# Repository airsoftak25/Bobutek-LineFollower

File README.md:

# Team
- Vadim Sobčuk - Modeling / Elektro
- Daniel Pelikán - Code / Elektro
- Luboš Stránský - PCB Manufacture
# Description
We are czech students from High school - prumyslova skola prosek - that enjoy making robots in the free time,

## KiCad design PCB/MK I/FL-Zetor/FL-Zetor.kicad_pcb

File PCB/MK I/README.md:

# About
This Folder Holds DWG file (edge cuts), exel files with components, gerber files (Main and Senzor) and Kicad Projects of LF-Zetro MKI 

Maded by Bobutek team with help from Otto von Bismax :D

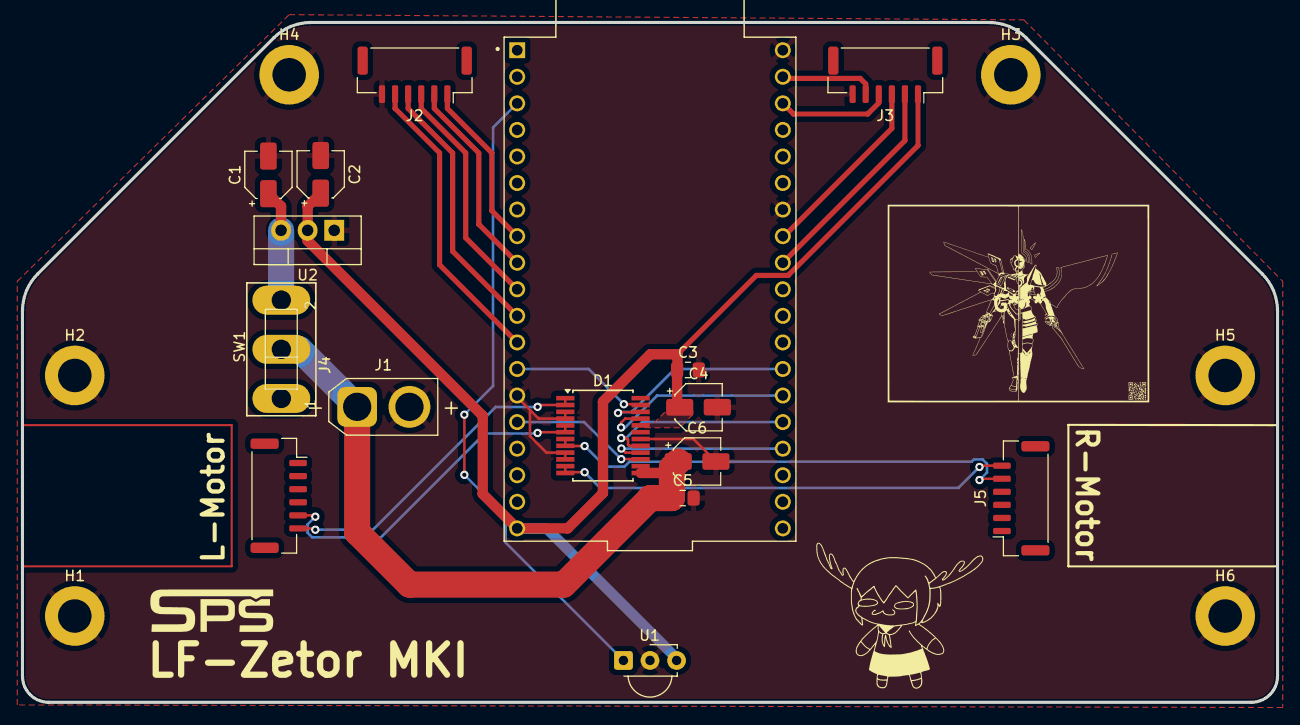
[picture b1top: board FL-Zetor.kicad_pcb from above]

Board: 2 copper layers, 120.0 x 65.0 mm, 22 parts (0 on the bottom side), 23 nets.

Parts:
C1, C2, C4, C6: 10uF; CP_Elec_4x5.4
C3, C5: 100nF; C_0805_2012Metric_Pad1.18x1.45mm_HandSolder
D1: TB6612FNG; SSOP-24_5.3x8.2mm_P0.65mm
H1, H2, H3, H4, H5, H6: MountingHole_Pad; MountingHole_3.2mm_M3_ISO7380_Pad
J1: Conn_01x02_Pin; AMASS_XT30U-F_1x02_P5.0mm_Vertical
J2, J3, J4, J5: Conn_01x06_Pin; JST_GH_SM06B-GHS-TB_1x06-1MP_P1.25mm_Horizontal
MCU1: DEVKIT_V1_ESP32-WROOM-32; MODULE_DEVKIT_V1_ESP32-WROOM-32
SW1: SL19; 255SB
U1: TSOP382xx; Vishay_MINICAST-3Pin
U2: LM1086; TO-220-3_Vertical

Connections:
+5V: C2.1, C3.1, C4.1, D1.20 (VCC), J3.1, MCU1.19 (EXT_5V), U1.3 (Vs), U2.2 (VO)
+12V: C1.1, C5.1, C6.1, D1.13 (VM2), D1.14 (VM3), D1.24 (VM1), J1.1, SW1.2 (B), SW1.3 (C), U2.3 (VI)
D-pin-ESP: MCU1.3 (SENSOR_VP), U1.1 (OUT)
D.M.C.A.1: D1.21 (AIN1), MCU1.25 (IO0)
D.M.C.A.2: D1.22 (AIN2), MCU1.26 (IO4)
D.M.C.B.1: D1.17 (BIN1), MCU1.24 (IO2)
D.M.C.B.2: D1.16 (BIN2), MCU1.23 (IO15)
GND: C1.2, C2.2, C3.2, C4.2, C5.2, C6.2, D1.3 (PGND1), D1.4 (PGND1), D1.9 (PGND2), D1.10 (PGND2), D1.18 (GND), H1.1, H2.1, H3.1, H4.1, H5.1, H6.1, J1.2, J2.6, J3.6, MCU1.14 (GND1), MCU1.32 (GND2), MCU1.38 (GND3), U1.2 (GND), U2.1 (ADJ)
LM1: D1.1 (AO1), D1.2 (AO1), J4.6
LM2: D1.5 (AO2), D1.6 (AO2), J4.5
PWM_A: D1.23 (PWMA), MCU1.13 (IO12)
PWM_B: D1.15 (PWMB), MCU1.15 (IO13)
RM1: D1.11 (BO1), D1.12 (BO1), J5.6
RM2: D1.7 (BO2), D1.8 (BO2), J5.5
S_D1: J2.5, MCU1.12 (IO14)
S_D2: J2.4, MCU1.11 (IO27)
S_D3: J2.3, MCU1.10 (IO26)
S_D4: J2.2, MCU1.9 (IO25)
S_D5: J2.1, MCU1.8 (IO33)
S_D6: J3.5, MCU1.37 (IO23)
S_D7: J3.4, MCU1.36 (IO22)
S_D8: J3.3, MCU1.31 (IO19)
S_D9: J3.2, MCU1.30 (IO18)

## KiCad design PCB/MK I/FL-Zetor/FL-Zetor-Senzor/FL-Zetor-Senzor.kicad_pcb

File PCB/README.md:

PCB for the line follower will be here
reffered to as MK and a number ascending from 1 to idk where will be the end but you get the gist of it
there will also be a folder for .lib stuff for kicad if you will be interested 
this may get updated or changed but i will try to keep it readable

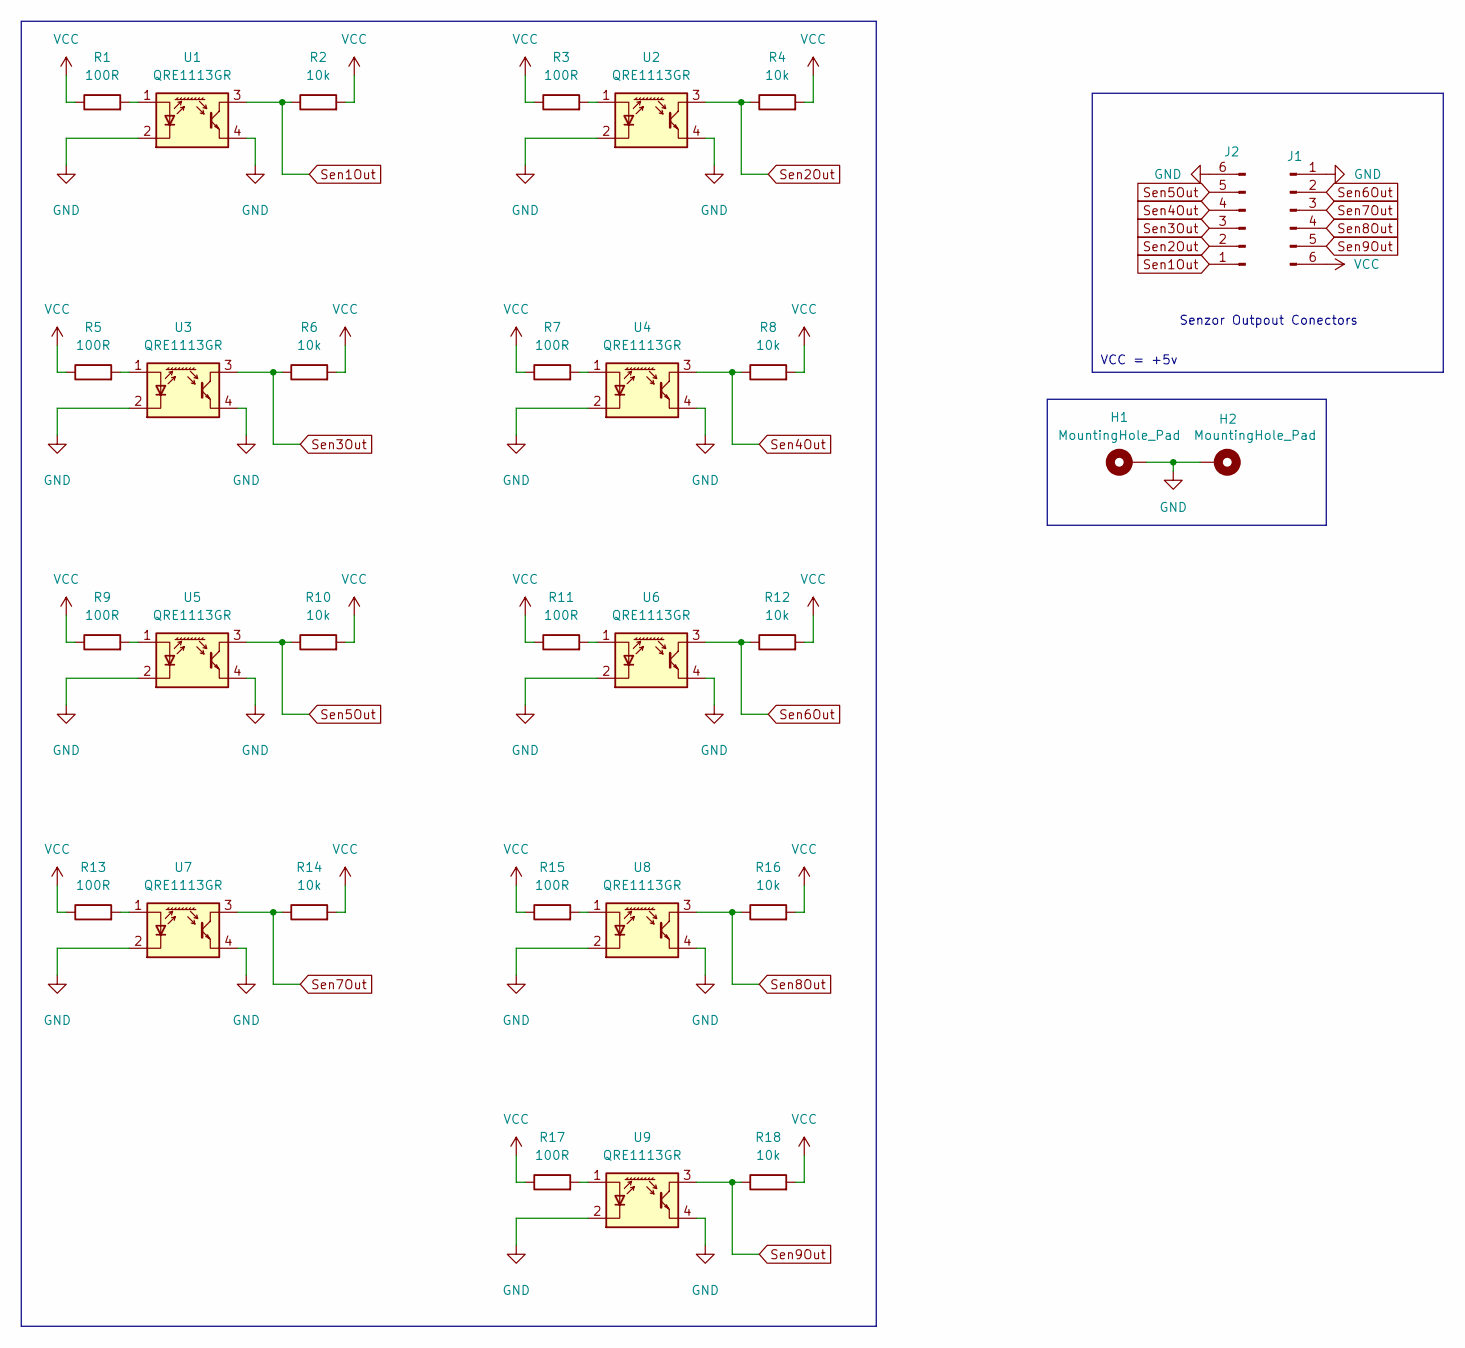
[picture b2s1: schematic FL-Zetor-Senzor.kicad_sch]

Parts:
H1, H2: MountingHole_Pad; MountingHole_3.2mm_M3_ISO7380_Pad
J1, J2: Conn_01x06_Pin; JST_GH_SM06B-GHS-TB_1x06-1MP_P1.25mm_Horizontal
R1, R3, R5, R7, R9, R11, R13, R15, R17: 100R; R_0805_2012Metric; LCSC C17408
R2, R4, R6, R8, R10, R12, R14, R16, R18: 10k; R_0805_2012Metric; LCSC C17414
U1, U2, U3, U4, U5, U6, U7, U8, U9: QRE1113GR; OnSemi_CASE100CY; LCSC C232862

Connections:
GND: H1.1, H2.1, J1.1, J2.6, U1.2 (K), U1.4, U2.2 (K), U2.4, U3.2 (K), U3.4, U4.2 (K), U4.4, U5.2 (K), U5.4, U6.2 (K), U6.4, U7.2 (K), U7.4, U8.2 (K), U8.4, U9.2 (K), U9.4
unnamed: R1.2, U1.1 (A)
unnamed: R3.2, U2.1 (A)
unnamed: R5.2, U3.1 (A)
unnamed: R7.2, U4.1 (A)
unnamed: R9.2, U5.1 (A)
unnamed: R11.2, U6.1 (A)
unnamed: R13.2, U7.1 (A)
unnamed: R15.2, U8.1 (A)
unnamed: R17.2, U9.1 (A)
Sen1Out: J2.1, R2.1, U1.3
Sen2Out: J2.2, R4.1, U2.3
Sen3Out: J2.3, R6.1, U3.3
Sen4Out: J2.4, R8.1, U4.3
Sen5Out: J2.5, R10.1, U5.3
Sen6Out: J1.2, R12.1, U6.3
Sen7Out: J1.3, R14.1, U7.3
Sen8Out: J1.4, R16.1, U8.3
Sen9Out: J1.5, R18.1, U9.3
VCC: J1.6, R1.1, R2.2, R3.1, R4.2, R5.1, R6.2, R7.1, R8.2, R9.1, R10.2, R11.1, R12.2, R13.1, R14.2, R15.1, R16.2, R17.1, R18.2

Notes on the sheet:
Senzor Outpout Conectors
VCC = +5v

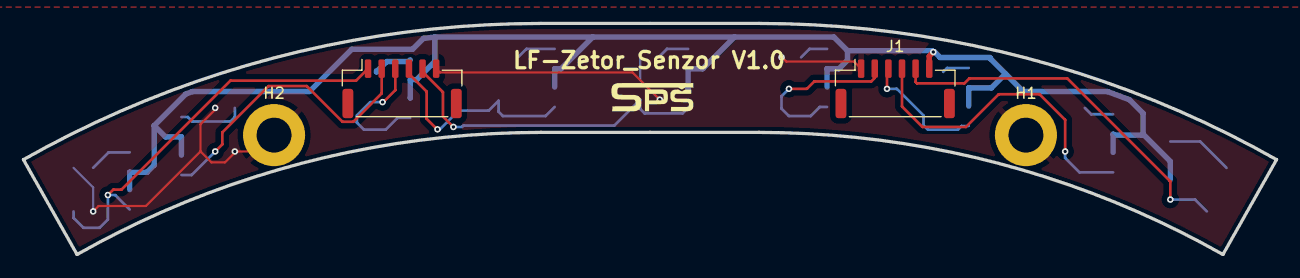
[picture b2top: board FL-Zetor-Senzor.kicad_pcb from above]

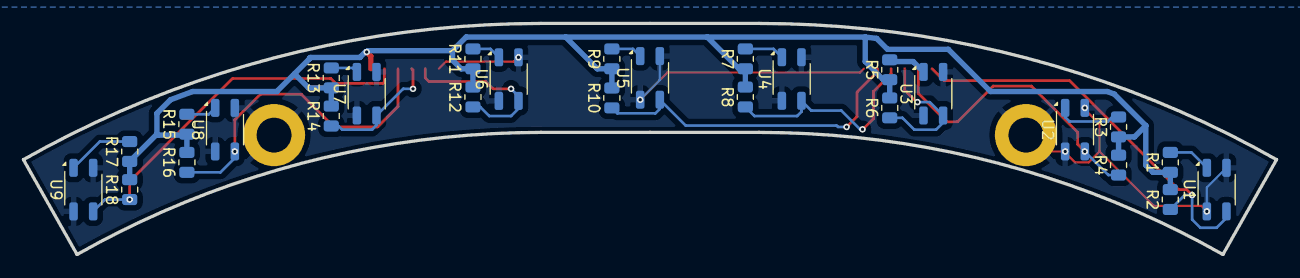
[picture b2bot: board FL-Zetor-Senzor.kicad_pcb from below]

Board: 2 copper layers, 115.0 x 21.2 mm, 31 parts (27 on the bottom side), 20 nets.

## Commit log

2025-04-15 Create test
2025-04-15 Create README.md
    Just test of readme
2025-04-15 Update README.md
    second test
2025-04-15 Update README.md
    finnaly i now wt to doo XD
2025-04-15 Create About
2025-04-15 Create nig
2025-04-15 Create OUTDATED
2025-04-15 Create Some word about it
2025-04-15 Update Some word about it
2025-04-22 Update about prototype
2025-04-22 Create folder competitions
2025-04-22 Create Docasny
2025-04-28 Update About
    pluh - prepis aboutu pro program
2025-04-28 Create cdcdc
2025-04-28 Create idkkkk
2025-04-28 Create penis
2025-04-28 Create M1 PSD WEIGHT
    psd weight system 1 module
2025-04-28 Update M1 PSD WEIGHT
    version 1, this is the base point from where we will be moving
2025-04-28 Create C++ About
    About for this folder
2025-04-28 Create About C++
    about for c++, may get updated
2025-04-28 Update About
    about for pcbs
2025-04-28 Update README.md
    update read me
2025-04-28 Create Z{zelva} PCB settup
    someone post the autocad there
2025-04-28 Create components-data-sheets
    pls pls
2025-04-28 Update About competitions
2025-04-28 Update About
2025-04-28 ja se zabiju
    nefunguje to vubec. ale dostal jsem zmrlinu takze asi pohoda
2025-04-28 jsem dement
    predelano na md soubor
2025-04-28 halooo
    co je
2025-04-28 yipie
    uz urcite vim co delat
2025-04-29 dxf import
    dwg do kicadu nefuguje potrenu dxf
2025-04-29 format change
    txt to md
2025-04-29 savva mi bije
    au
2025-04-29 Upload Držák motoru
2025-04-29 Upload new Main Edge Cut and other things
2025-04-29 ehmm
    joo
2025-04-29 uprava more
2025-04-29 ki cad bs
    bs
2025-04-29 negr
2025-04-29 ki cad
    things
2025-04-29 ki cad
    savva mi bnarval do prdele curaka
2025-04-30 redesighn edge cuts
2025-05-06 pluh
    mk update
2025-05-06 ehhh
    eeeeh
2025-05-06 saveee
    s
2025-05-07 Patch some shits
    Potřeby jemně předělat senzor
2025-05-08 pcb shit
2025-05-08 rename pcb files
2025-05-09 pcbs done
    that pieces of craps is done
2025-05-09 update for senzot + grb files
2025-05-14 gabriel
    gabriel
2025-05-15 some shit
2025-05-15 just lol
